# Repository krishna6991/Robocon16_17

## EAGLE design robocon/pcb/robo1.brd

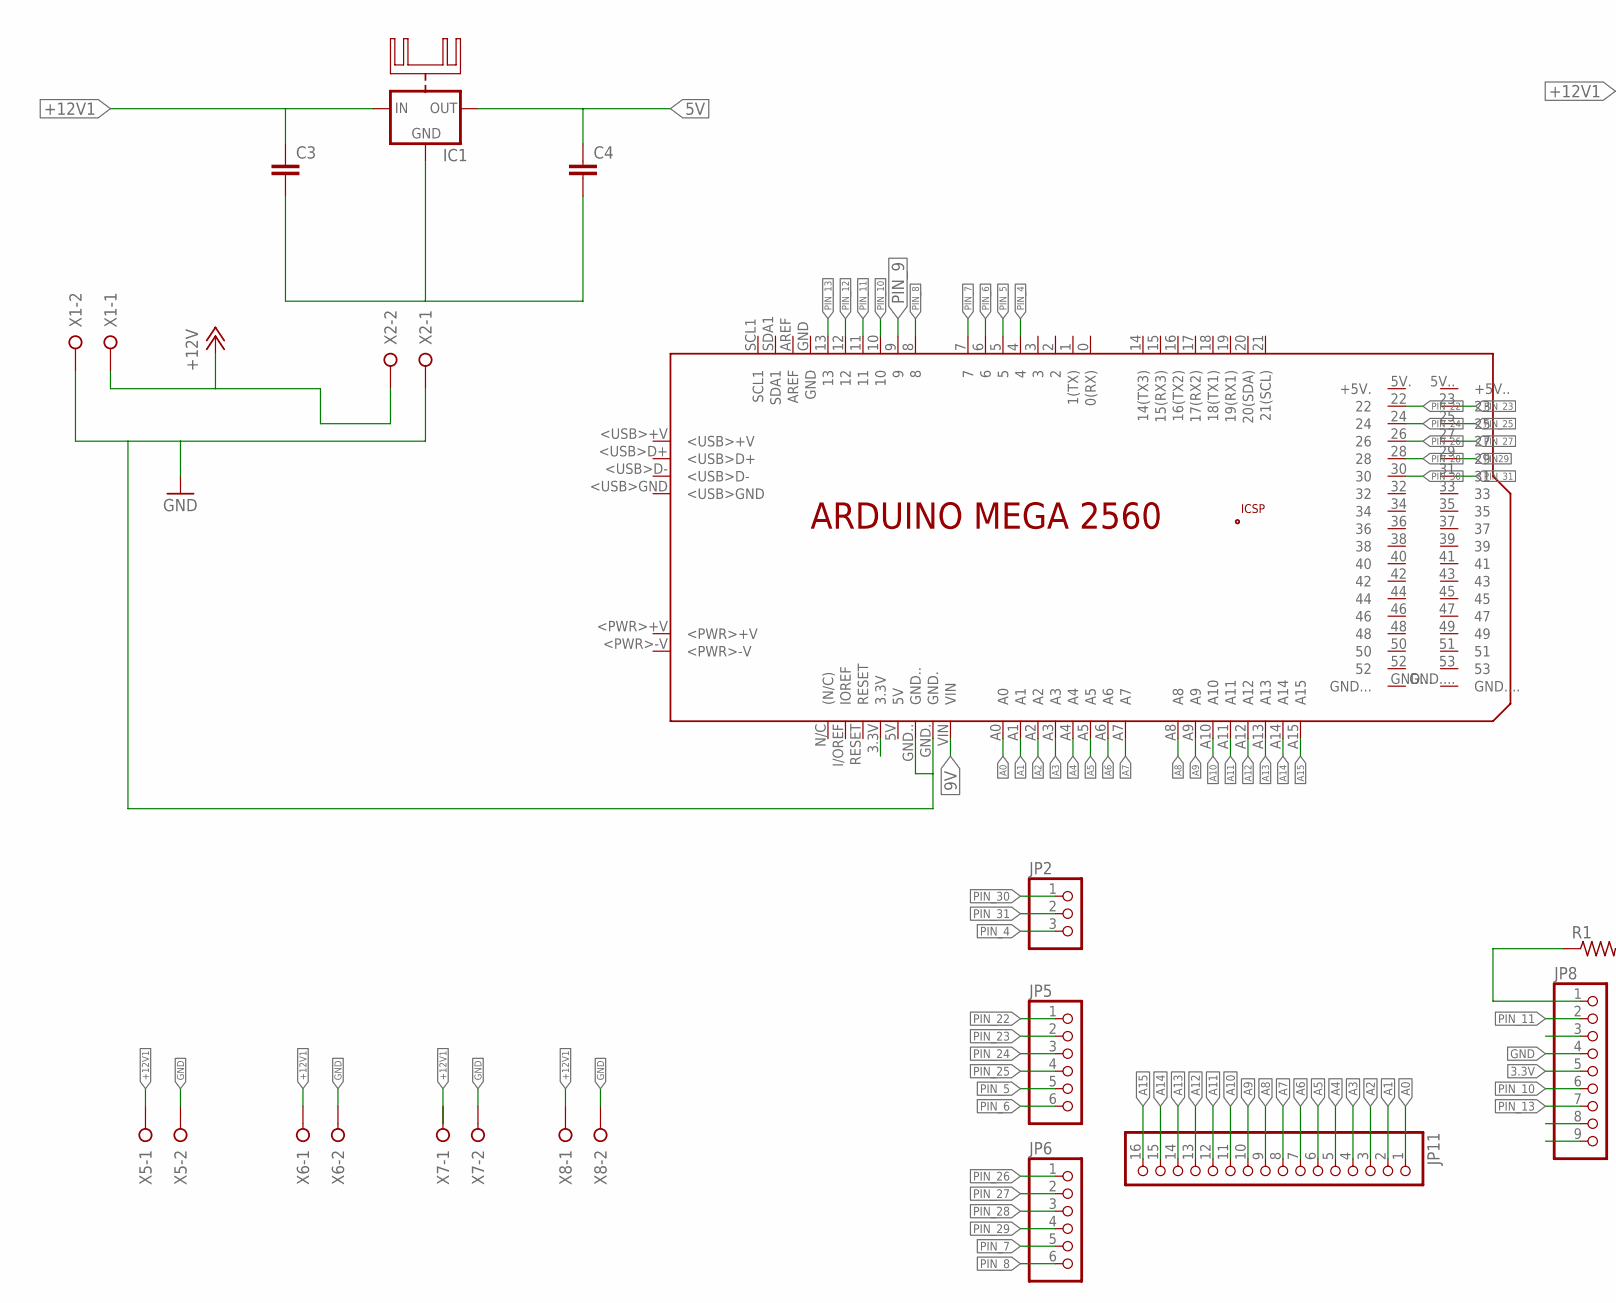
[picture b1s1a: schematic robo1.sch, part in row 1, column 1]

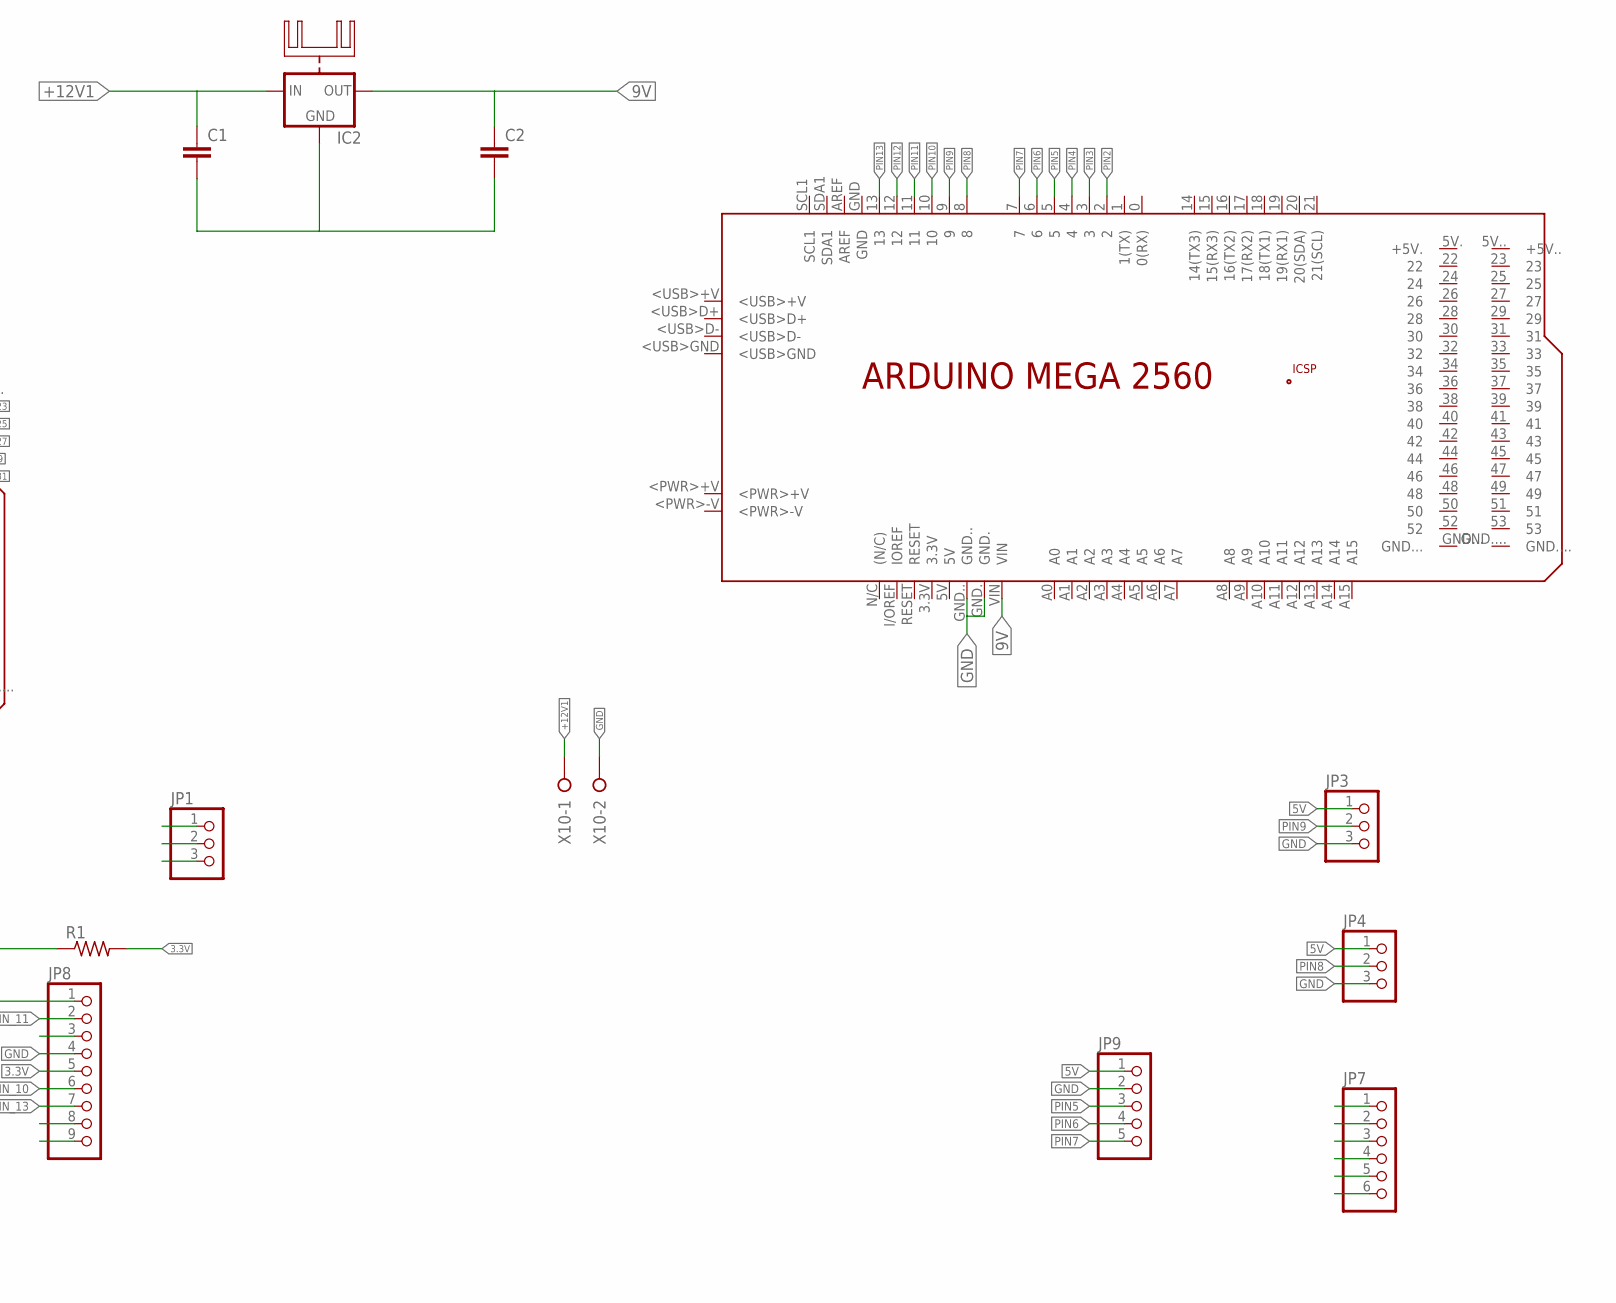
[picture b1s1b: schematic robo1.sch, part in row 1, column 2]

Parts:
C1, C2, C3, C4: C5/2.5; C5B2.5
IC1, IC2: 78XXH
JP1, JP2, JP3, JP4: PINHD-1X3; 1X03
JP5, JP6, JP7: PINHD-1X6; 1X06
JP8: PINHD-1X9; 1X09
JP9: PINHD-1X5; 1X05
JP11: PINHD-1X16; 1X16
MEGA1, MEGA2: ARDUINO_MEGA2560
R1: R-US_0207/10; 0207/10
X1, X2, X5, X6, X7, X8, X10: W237-02P; W237-132

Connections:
3.3V: JP8.5, MEGA1.3.3V, R1.2
5V: C4.1, IC1.OUT, JP3.1, JP4.1, JP9.1
9V: C2.1, IC2.OUT, MEGA1.VIN, MEGA2.VIN
+12V: X1.1, X2.2
+12V1: C1.1, C3.1, IC1.IN, IC2.IN, X5.1, X6.1, X8.1, X10.1
A0: JP11.1, MEGA1.A0
A1: JP11.2, MEGA1.A1
A2: JP11.3, MEGA1.A2
A3: JP11.4, MEGA1.A3
A4: JP11.5, MEGA1.A4
A5: JP11.6, MEGA1.A5
A6: JP11.7, MEGA1.A6
A7: JP11.8, MEGA1.A7
A8: JP11.9, MEGA1.A8
A9: JP11.10, MEGA1.A9
A10: JP11.11, MEGA1.A10
A11: JP11.12, MEGA1.A11
A12: JP11.13, MEGA1.A12
A13: JP11.14, MEGA1.A13
A14: JP11.15, MEGA1.A14
A15: JP11.16, MEGA1.A15
GND: C1.2, C2.2, C3.2, C4.2, IC1.GND, IC2.GND, JP1.1, JP3.3, JP4.3, JP8.4, JP9.2, MEGA1.GND., MEGA1.GND.., MEGA2.GND., MEGA2.GND.., X1.2, X2.1, X5.2, X6.2, X7.2, X8.2, X10.2
PIN2: JP7.1, MEGA2.2
PIN3: JP7.2, MEGA2.3
PIN4: MEGA2.4
PIN5: JP9.3, MEGA2.5
PIN6: JP9.4, MEGA2.6
PIN7: JP9.5, MEGA2.7
PIN8: JP4.2, MEGA2.8
PIN9: JP3.2, MEGA2.9
PIN10: JP7.3, MEGA2.10
PIN11: JP7.4, MEGA2.11
PIN12: JP7.5, MEGA2.12
PIN13: JP7.6, MEGA2.13
PIN_4: JP2.3, MEGA1.4
PIN_5: JP5.5, MEGA1.5
PIN_6: JP5.6, MEGA1.6
PIN_7: JP6.5, MEGA1.7
PIN_8: JP6.6, MEGA1.8
PIN_9: JP1.3, MEGA1.9
PIN_10: JP8.6, MEGA1.10
PIN_11: JP8.2, MEGA1.11
PIN_12: JP8.1, MEGA1.12, R1.1
PIN_13: JP8.7, MEGA1.13
PIN_22: JP5.1, MEGA1.22
PIN_23: JP5.2
PIN_24: JP5.3, MEGA1.24
PIN_25: JP5.4
PIN_26: JP6.1, MEGA1.26
PIN_27: JP6.2
PIN_28: JP6.3, MEGA1.28
PIN_29: JP6.4
PIN_30: JP2.1, MEGA1.30
PIN_31: JP2.2

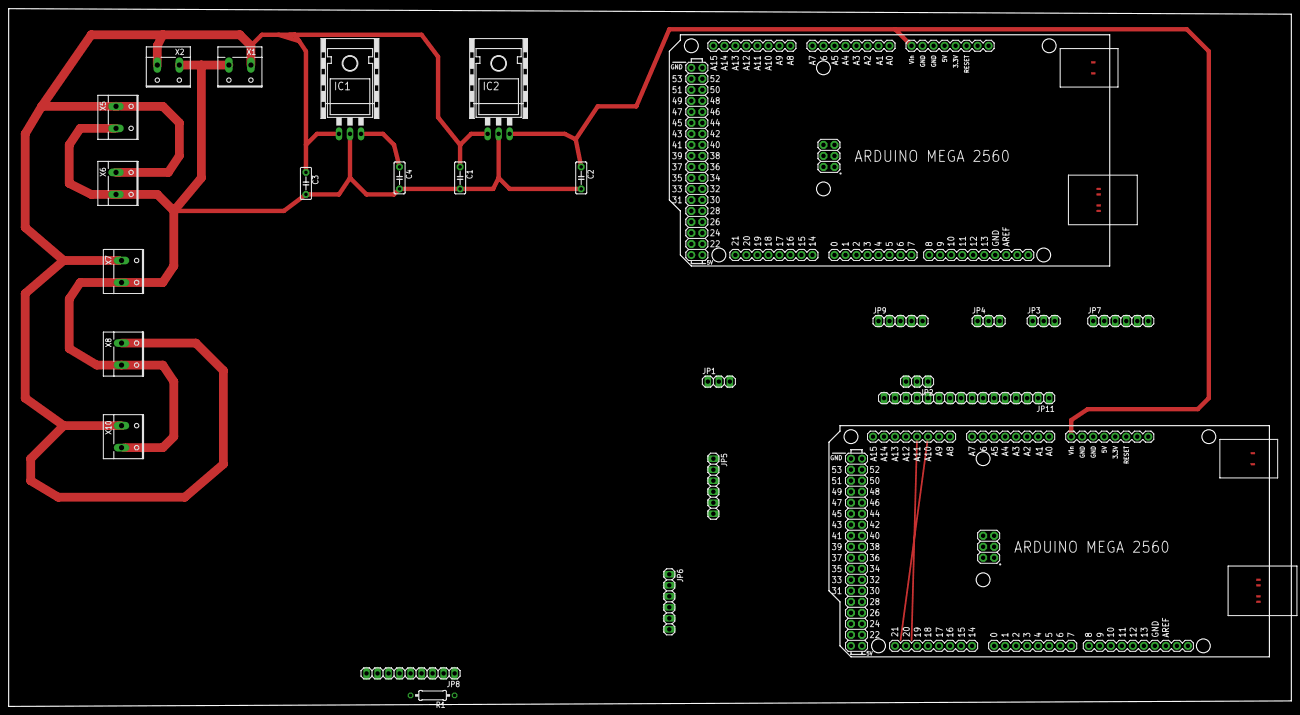
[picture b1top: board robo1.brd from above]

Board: 2 copper layers, 295.9 x 161.0 mm, 26 parts (0 on the bottom side), 48 nets.

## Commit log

2017-10-15 robocon codes
